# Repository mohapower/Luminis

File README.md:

# Luminis

**Fényerő kapcsolási határérték beállítása:**
1. Soros monitor megnyitása
  - Hardver csatlakoztatása usb kábbellel a számítógéphez
  - Arduino Ide megnyitása
  - Port beállítása: Menüsorvól: Eszközök/Port --> megfelelő port kiválasztása
  - Soros Monitor megnyitása: Eszközök/Soros monitor vagy Ctrl+Shift+M
  - Jobb alsó sarokban a "nincs sorvég" és "9600 baud" legyen beállítva
  - Ha minden működik, akkor a következő adatok jelennek meg másodpercenként:
    - Mert fenyero: 158
    - A beallitott kapcsolasi hatarartek: 333
    - Sotet van/Világos van
    
2. Fényerő kapcsolási határérték beállítása:
  - Bal felső beviteli mezőbe írjuk be az új kapcsolási határértéket, 0-1023 közötti értékek megfelelőek
  - Nomjuk meg a külség gombot (enter), a következő jelenik meg:
    - Az uj kapcsolasi hatarertek: 777
    - Mert fenyero: 232
    - A beallitott kapcsolasi hatarartek: 777
    - Sotet van

Amennyiben a mert fényerő alacsonyabb mit a beállított, az eszköt azt érzékeli, hogy sötét van. Vagyis ha a kapcsolási határértéket növeljük, a világítás előbb (nagyobb fénynél) fog kapcsolni.

**Firmware frissítés:**
Open your sketch
Open the IdoRele.ino

Select your board type and port
Select Tools > Board > Arduino AVR Boards > Arduino Nano.

NOTE: We have updated the Nano board with a fresh bootloader. 
Boards sold by us from January 2018 have this new bootloader, while boards manufactured before that date have the old bootloader. 
First, check that Tools > Board > Boards Manager shows you have the Arduino AVR Boards 1.16.21 or later installed. 
Then, to program the NEW Arduino NANO boards you need to chose Tools > Processor > ATmega328P. 
To program old boards you need to choose Tools > Processor > ATmega328P (Old Bootloader). 
If you get an error while uploading or you are not sure which bootloader you have, try each Tools > Processor menu option until your board gets properly programmed.

Upload and Run your first Sketch
To upload the sketch to the Arduino Nano, click the Upload button in the upper left to load and run the sketch on your board:

UNO Upload

Wait a few seconds - you should see the RX and TX LEDs on the board flashing. 
If the upload is successful, the message "Done uploading." will appear in the status bar.

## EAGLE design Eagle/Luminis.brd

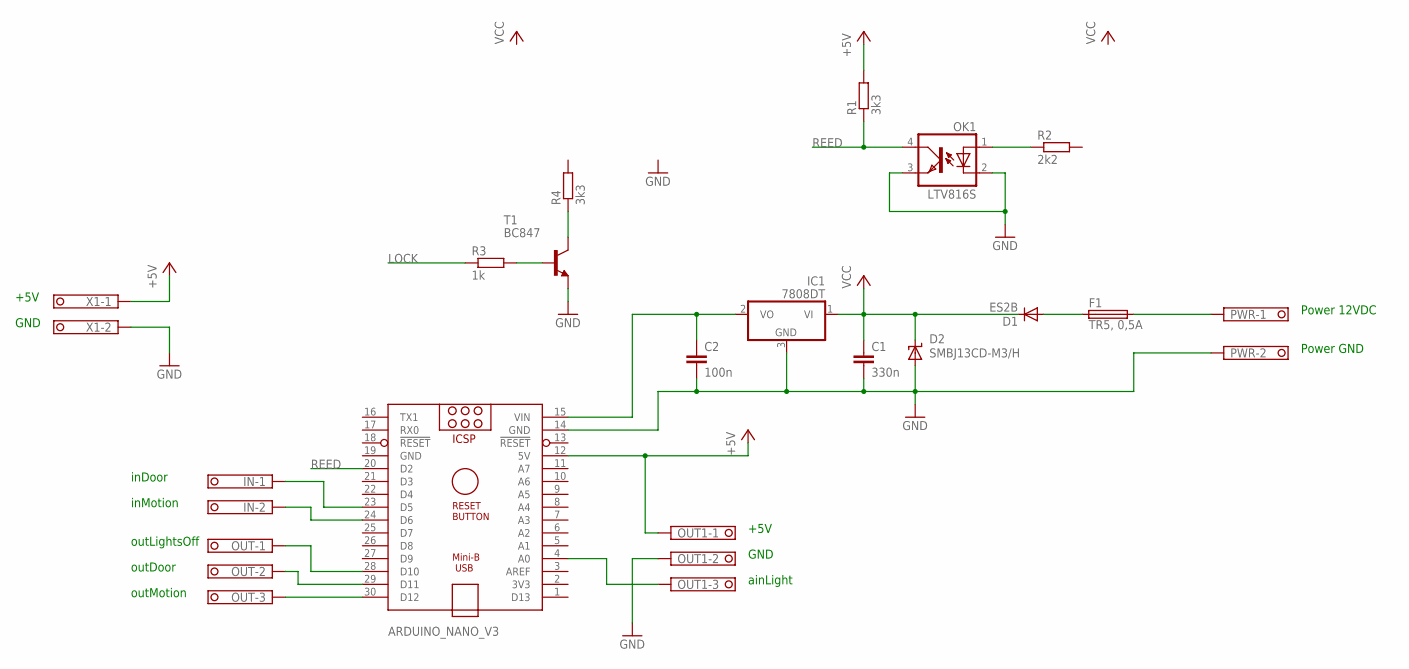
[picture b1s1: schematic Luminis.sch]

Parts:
ARDUINO_NANO_V3: ARDUINO_NANO
C1: 330n; C1206
C2: 100n; C1206
D1: ES2B; SMB
D2: SMBJ13CD-M3/H; SMBJ
F1: TR5, 0,5A; TR5
IC1: 7808DT; TO252
IN: 1751248
OK1: LTV816S; DIL4-SMD
OUT, OUT1: 1751251
PWR: 1751248
R1, R4: 3k3; R1206
R2: 2k2; R1206
R3: 1k; R1206
T1: BC847; SOT23
X1: 1751248

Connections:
+5V: ARDUINO_NANO_V3.12 (5V), OUT1.1, R1.2, X1.1
GND: ARDUINO_NANO_V3.14 (GND), ARDUINO_NANO_V3.19 (GND), C1.2, C2.2, D2.A, IC1.3 (GND), OK1.2 (C), OK1.3 (EMIT), OUT1.2, PWR.2, T1.2 (E), X1.2
LOCK: R3.1
unnamed: ARDUINO_NANO_V3.4 (A0), OUT1.3
unnamed: OK1.1 (A), R2.1
unnamed: ARDUINO_NANO_V3.30 (D12), OUT.3
unnamed: R4.1, T1.3 (C)
unnamed: F1.2, PWR.1
unnamed: ARDUINO_NANO_V3.29 (D11), OUT.2
unnamed: ARDUINO_NANO_V3.28 (D10), OUT.1
unnamed: ARDUINO_NANO_V3.24 (D6), IN.2
unnamed: ARDUINO_NANO_V3.23 (D5), IN.1
unnamed: R3.2, T1.1 (B)
unnamed: D1.A, F1.1
unnamed: ARDUINO_NANO_V3.15 (VIN), C2.1, IC1.2 (VO)
REED: ARDUINO_NANO_V3.20 (D2), OK1.4 (COL), R1.1
VCC: C1.1, D1.C, D2.C, IC1.1 (VI)

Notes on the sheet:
Power 12VDC
Power GND
outLightsOff
outMotion
outDoor
inDoor
inMotion
ainLight
GND
+5V

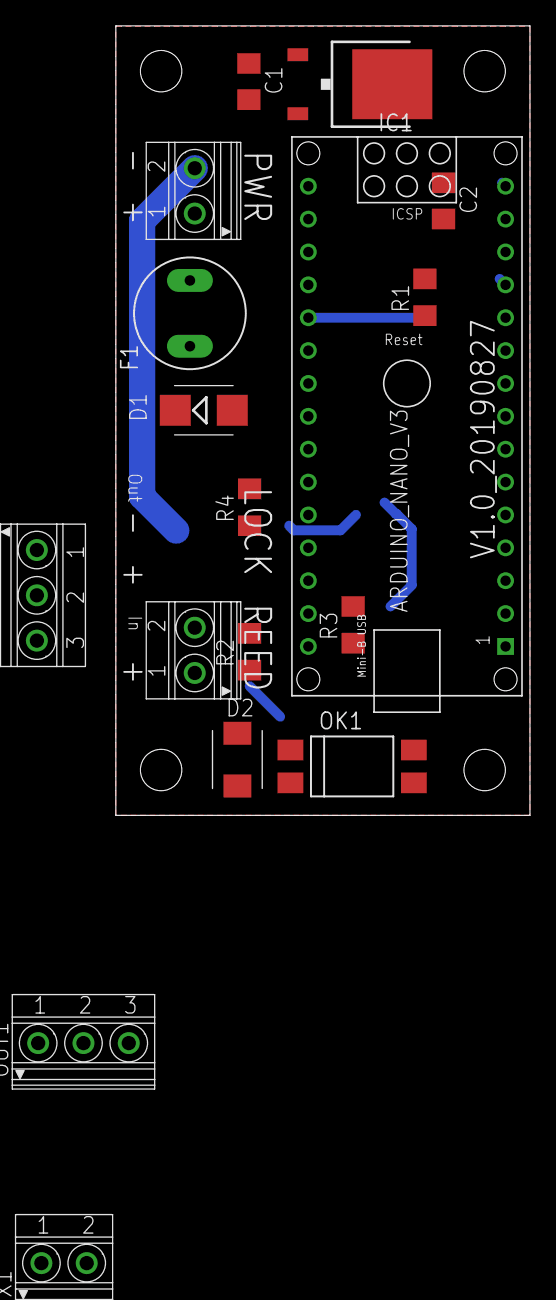
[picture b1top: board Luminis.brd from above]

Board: 2 copper layers, 32.0 x 61.0 mm, 18 parts (1 on the bottom side), 16 nets.

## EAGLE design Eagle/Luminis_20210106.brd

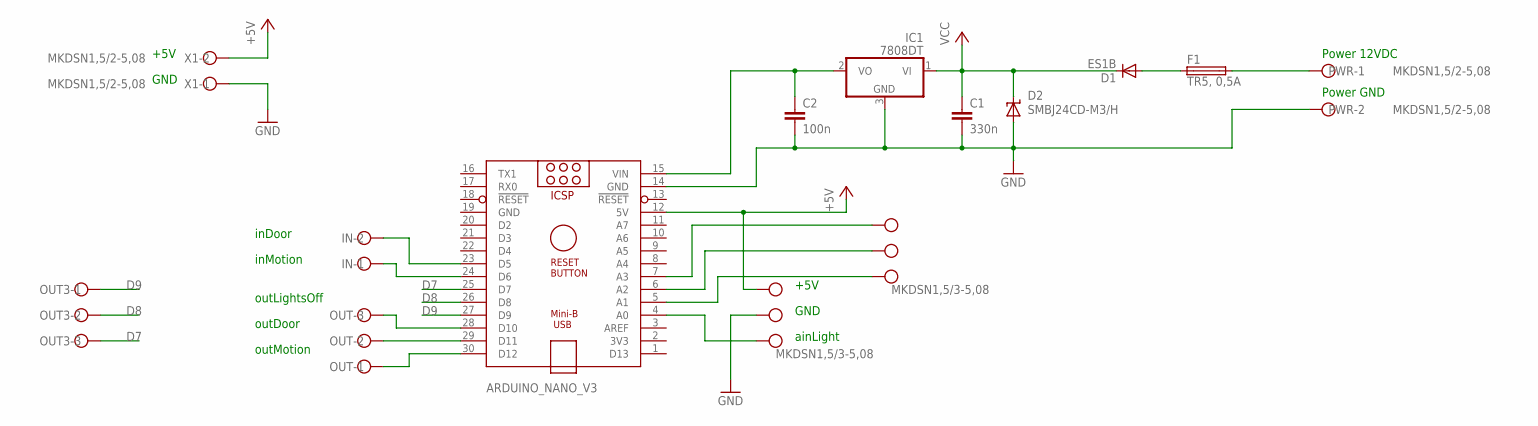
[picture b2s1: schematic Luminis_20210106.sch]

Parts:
ARDUINO_NANO_V3: ARDUINO_NANO
C1: 330n; C1206
C2: 100n; C1206
D1: ES1B; DO214AC
D2: SMBJ24CD-M3/H; SMBJ
F1: TR5, 0,5A; TR5
IC1: 7808DT; TO252
IN: MKDSN1,5/2-5,08
OUT, OUT1, OUT2, OUT3: MKDSN1,5/3-5,08
PWR: MKDSN1,5/2-5,08
X1: MKDSN1,5/2-5,08

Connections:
+5V: ARDUINO_NANO_V3.12 (5V), OUT1.1, X1.2
D7: ARDUINO_NANO_V3.25 (D7), OUT3.3
D8: ARDUINO_NANO_V3.26 (D8), OUT3.2
D9: ARDUINO_NANO_V3.27 (D9), OUT3.1
GND: ARDUINO_NANO_V3.14 (GND), ARDUINO_NANO_V3.19 (GND), C1.2, C2.2, D2.A, IC1.3 (GND), OUT1.2, PWR.2, X1.1
unnamed: ARDUINO_NANO_V3.4 (A0), OUT1.3
unnamed: ARDUINO_NANO_V3.5 (A1), OUT2.3
unnamed: ARDUINO_NANO_V3.30 (D12), OUT.1
unnamed: ARDUINO_NANO_V3.6 (A2), OUT2.2
unnamed: F1.2, PWR.1
unnamed: ARDUINO_NANO_V3.29 (D11), OUT.2
unnamed: ARDUINO_NANO_V3.28 (D10), OUT.3
unnamed: ARDUINO_NANO_V3.7 (A3), OUT2.1
unnamed: ARDUINO_NANO_V3.24 (D6), IN.1
unnamed: ARDUINO_NANO_V3.23 (D5), IN.2
unnamed: D1.A, F1.1
unnamed: ARDUINO_NANO_V3.15 (VIN), C2.1, IC1.2 (VO)
VCC: C1.1, D1.C, D2.C, IC1.1 (VI)

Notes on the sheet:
Power 12VDC
Power GND
outLightsOff
outMotion
outDoor
inDoor
inMotion
ainLight
GND
+5V

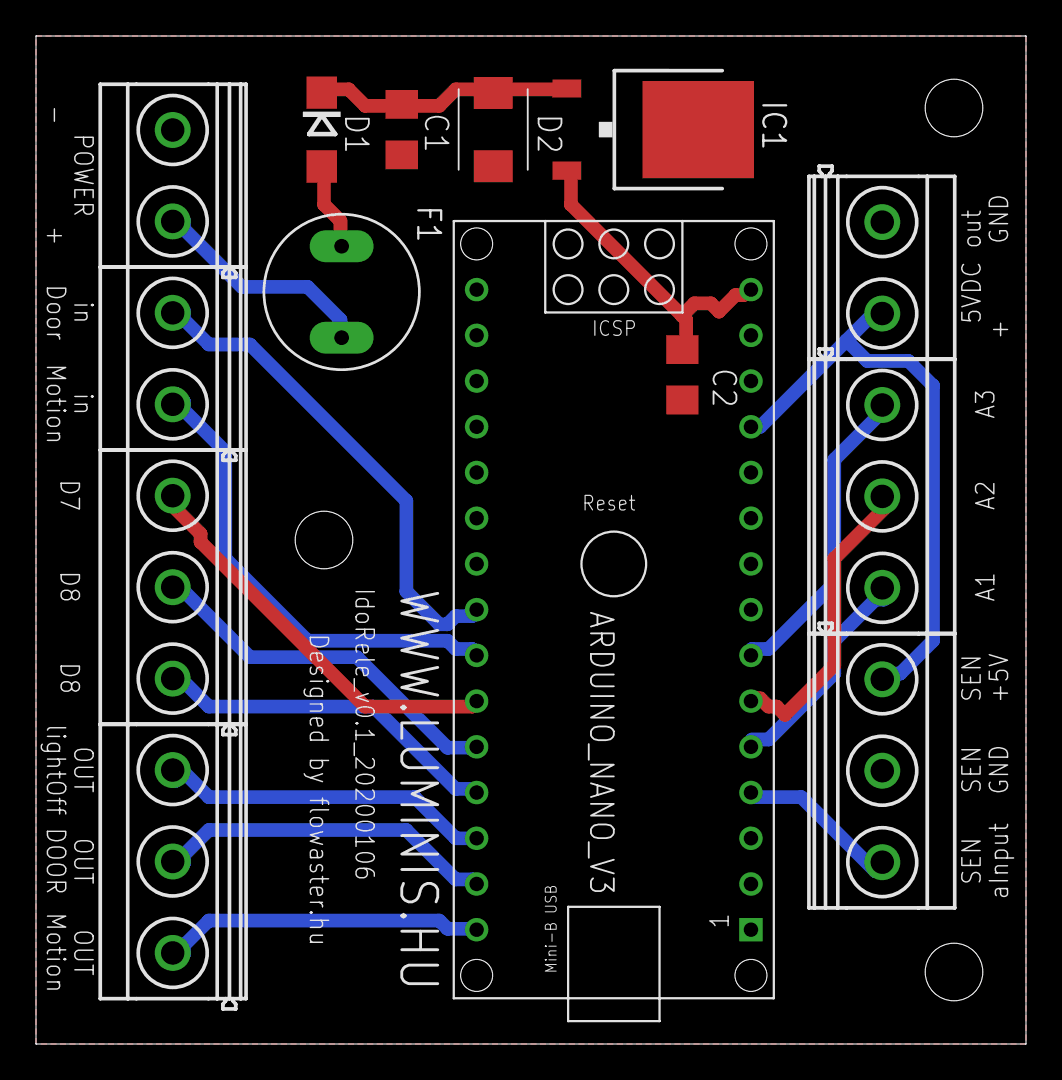
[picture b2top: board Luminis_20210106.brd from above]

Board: 2 copper layers, 55.0 x 56.0 mm, 14 parts (0 on the bottom side), 18 nets.

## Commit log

2020-11-10 Add project files
2020-11-10 Update Docs
2020-11-17 Ha nappal felkapcsolják kézzel, akkor is lehapcsol a beállított idő után, ha nincs mozgás
2021-02-22 Finished
2021-03-30 Add BOM
2021-04-23 Atadott verzio
2021-07-20 - add eplan project - add corridor light relay
2021-07-23 Atadva
